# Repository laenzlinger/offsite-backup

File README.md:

# Granit — Offsite Backup Device

Custom carrier board for the Raspberry Pi CM4 Compute Module, designed as a minimal offsite backup appliance.

## Concept

A compact, headless device that connects to a remote network and receives encrypted backups onto an attached hard disk.
Designed to be left at a trusted offsite location (friend's house, office, etc.) and managed remotely.

This PCB is designed with [KiCad 10](https://www.kicad.org/blog/2026/03/Version-10.0.0-Released/)

## Hardware

### Core Components

| Component | Description |
|---|---|
| Raspberry Pi CM4 | Compute module (PCIe Gen 2 x1). CM5 mechanically compatible but not validated for power budget |
| ASM1061 | PCIe Gen 2 x1 to 2-port SATA III controller (no firmware blob required) |
| 2.5" or 3.5" SATA HDD/SSD | Backup storage |
| Amphenol 10029364-001LF | 22-pin SATA connector (data 7-pin + power 15-pin), right-angle |
| RJ45 + Ethernet magnetics | Gigabit Ethernet |
| DS3231 RTC | Battery-backed real-time clock with alarm wake (I2C) |
| CR2032 coin cell | RTC backup battery |
| RGB LED | Status indicator (idle/backup/error/maintenance) |
| Tactile button | Manual shutdown, trigger backup, enter maintenance mode on boot |
| Hirose DF40C-100DS-0.4V(51) | 2x CM4 board-to-board connectors |
| AP64501SP-13 | 3.5A DC-DC buck converter (reused from [pedalboard-hw](https://github.com/pedalboard/pedalboard-hw)) |
| USB-C | USB 2.0 OTG connector with USBLC6-2SC6 ESD protection |
| 2N7002 + 74AHCT1G32 | Hardware wake circuit (RTC alarm → GLOBAL_EN) and SATA power gate drivers |

### Block Diagram

### PCB 3D Render

### Key Design Decisions

- **ASM1061 over USB-to-SATA bridges**: Native PCIe SATA controller using the standard Linux
  `ahci` driver. No proprietary firmware blob required — the SPI flash footprint can be left
  unpopulated. SMART works natively (`smartctl /dev/sda`) without SAT translation hacks.
  Both CM4 and CM5 have PCIe Gen 2 x1, so full SATA III throughput is available on either
  module — unlike USB-to-SATA, which would be bottlenecked by CM4's USB 2.0 (~35 MB/s).
- **12V DC input**: Required for 3.5" HDD support (spindle motor needs 12V).
  12V is passed through directly to the SATA power connector.
  AP64501SP-13 accepts 3.8–28V input, so 12V is well within range.
  Both barrel jack (Würth 6941xx301002) and screw terminal (Phoenix MKDS-1,5-2) footprints
  are provided — populate one at assembly time.
- **Reuse from pedalboard-hw**: CM connector, power supply (AP64501SP-13 buck + NCP1117 LDO),
  USB power switch (AP2553W6), KiCad symbol/footprint library, CI pipeline.
- **USB-C OTG**: Single USB-C connector for eMMC flashing (`rpiboot`) and USB mass storage
  gadget mode (initial backup seeding over USB). USB 2.0 device mode only, with USBLC6-2SC6
  ESD protection.
- **SATA power control**: 12V and 5V to the SATA connector are software-controlled via
  GPIO17. HDD is off by default at boot — powered on explicitly by software. Solder jumpers
  (JP5, JP6) allow changing the default to power-on at boot without a PCB respin.
- **Power budget**: 12V @ 2A (3.5" HDD spin-up) + 5V @ 2.3A peak (CM4 + electronics) — use a 12V/3A+ PSU.
- **Boot and storage strategy**: Full OS on CM4 eMMC (no SD card slot), SATA HDD dedicated
  to LUKS-encrypted backup storage only. HDD can spin down when idle. No SD card — eMMC is
  more reliable for a deploy-and-forget device. Reflashing via `nRPIBOOT` + USB-C if needed.

For detailed circuit design notes, PCB routing guidelines, and netclass definitions,
see [hardware/DESIGN.md](hardware/DESIGN.md).

## Software

The device runs Raspberry Pi OS Lite (headless).

### Planned Stack

- Restic backup repository (encryption built-in)
- rsync to receive backups from NAS
- `smartmontools` for disk health monitoring (`smartctl /dev/sda`)
- WireGuard VPN for remote management
- RTC-based scheduled wake: DS3231 alarm → GPIO4 interrupt → CM wakes from suspend → backup runs → suspend
  (`GLOBAL_EN` tied high via pull-up, CM4 uses Linux `rtcwake` for suspend/resume.
  Hardware power-off wake via MOSFET latch on `GLOBAL_EN` planned for v2.)
- LUKS full-disk encryption on the backup drive
- Automatic drive mount and health monitoring

### HDD Power Control

GPIO17 (`SATA_PWR_EN`) controls the P-FET power switches for the SATA 12V and 5V rails.
The boot default is selected by solder jumpers JP5 and JP6 (see Design Considerations above).

**Connect sequence** (power on → detect → mount):
```bash
#!/bin/bash
# Power on SATA rails (GPIO high → N-FET on → P-FET gate low → P-FET on)
gpioset gpiochip0 17=1
sleep 2

# Rescan AHCI bus (ASM1061 hot-plug)
echo "- - -" > /sys/class/scsi_host/host0/scan
sleep 3

# Unlock and mount
cryptsetup luksOpen /dev/sda1 backup
mount /dev/mapper/backup /mnt/backup
```

**Disconnect sequence** (unmount → spin down → power off):
```bash
#!/bin/bash
# Unmount and close LUKS
umount /mnt/backup
cryptsetup luksClose backup

# Spin down platters
hdparm -Y /dev/sda
sleep 1

# Remove SCSI device before power cut
echo 1 > /sys/block/sda/device/delete

# Power off SATA rails (GPIO low → N-FET off → pull-up → P-FET off)
gpioset gpiochip0 17=0
```

### Deployment

1. Initial backup on-site: connect Granit to local network, run full backup over LAN
2. Move device to offsite location (friend's house, office, etc.)
3. Plug in Ethernet + power — done
4. Subsequent backups are incremental and run automatically over WireGuard

### Monitoring & Alerting

Monitoring must live outside the Granit device — if the device fails, it can't alert about
its own failure. The device reports in after each backup run using a dead man's switch pattern:

- After each successful backup, Granit pings a healthcheck endpoint (e.g. self-hosted or healthchecks.io)
- If the expected ping doesn't arrive, an alert is triggered (email, push notification)
- Reported metrics: backup success/failure, SMART disk health, disk space remaining
- WireGuard connectivity is implicitly monitored — no tunnel means no ping

## Enclosure

Metal enclosure designed for a plug-and-forget deployment. The device should be installable
by a non-technical person: plug in Ethernet, plug in power, done.

### Hammond 1455 Series

Same PCB (92 × 100mm) fits both cases, held by a 3D printed internal frame.
PCB and HDD sit side-by-side along the enclosure length, SATA connector direct-mates between them.

| | 1455L2201 (Slim) | 1455T2601 (Wide) |
|---|---|---|
| Dimensions | 220 × 103 × 30.5 mm | 260 × 160 × 51.5 mm |
| Internal width | ~100 mm | ~157 mm |
| Internal height | ~27 mm | ~48 mm |
| HDD support | 2.5" only | 2.5" or 3.5" |
| Material | Extruded aluminium | Extruded aluminium |
| Colors | Natural, Black, Blue, Red | Natural, Black, Blue, Red |
| Assembly |  |  |

### Requirements

- Cutouts: barrel jack or screw terminal (12V), RJ45 (Ethernet), USB-C
- Tactile button accessible from outside (recessed to prevent accidental press)
- RGB LED visible through enclosure (light pipe or translucent window)
- Thermal pad or heatsink contact for CM4 SoC to enclosure lid
- Internal mounting for 2.5" or 3.5" HDD (M4 mounting holes)
- PCB standoffs (M3 mounting holes)

## Generated Hardware Documentation

Browse the latest generated outputs at **[laenzlinger.github.io/granit](https://laenzlinger.github.io/granit/)**.

Includes schematic PDF, interactive BOM, HTML BOM, and PCB prints — auto-generated on every push with [KiBot](https://github.com/INTI-CMNB/KiBot) (dev branch) running inside the official [kicad/kicad:10.0](https://hub.docker.com/r/kicad/kicad) container.

## License

[CERN Open Hardware Licence Version 2 - Permissive](https://ohwr.org/cern_ohl_p_v2.txt)

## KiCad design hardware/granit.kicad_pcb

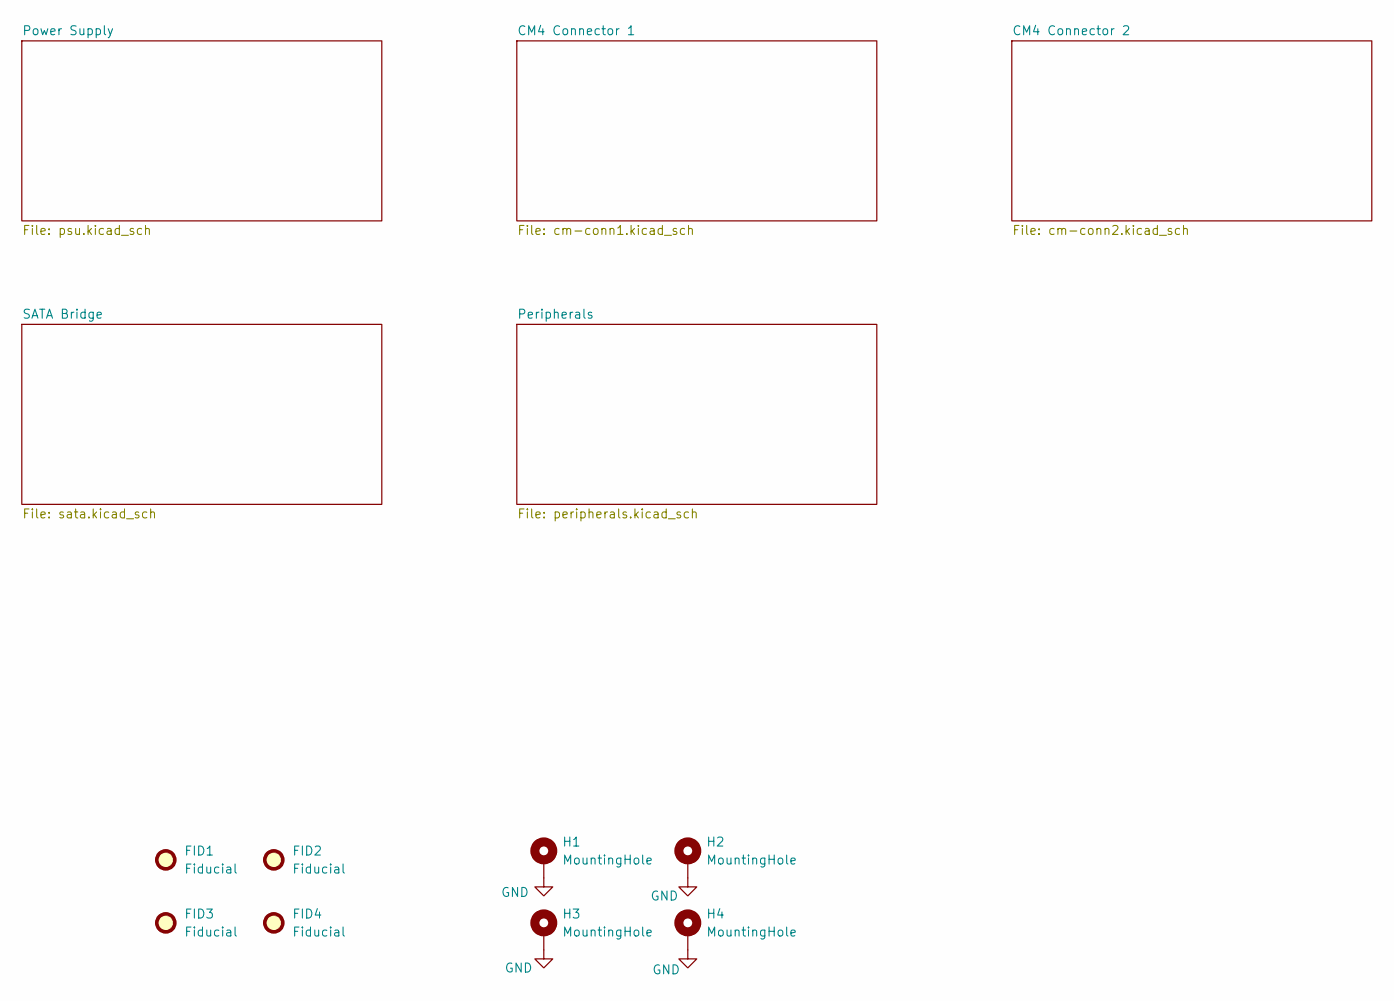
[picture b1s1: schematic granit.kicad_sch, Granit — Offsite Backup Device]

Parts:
FID1, FID2, FID3, FID4: Fiducial; Fiducial_1mm_Mask2mm
H1, H2, H3, H4: MountingHole; MountingHole_3.2mm_M3_Pad_Via

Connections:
GND: H1.1 (1_1), H2.1 (1_1), H3.1 (1_1), H4.1 (1_1); also elsewhere on the board

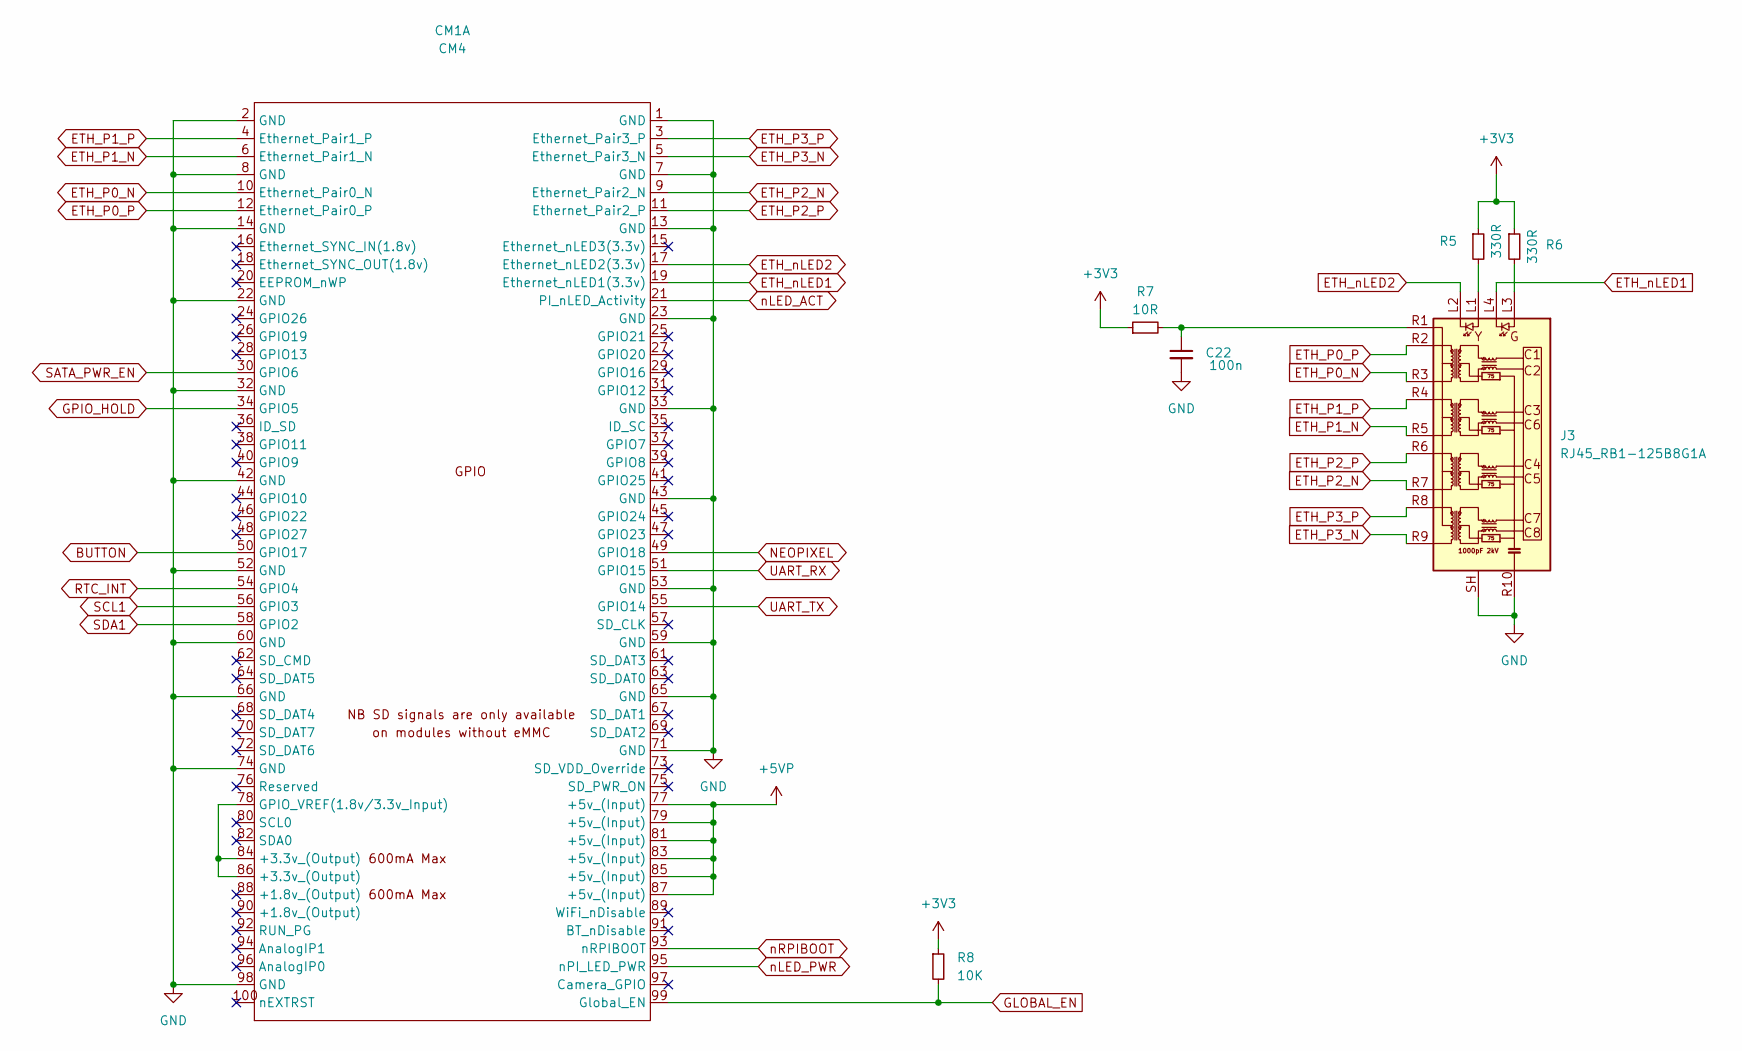
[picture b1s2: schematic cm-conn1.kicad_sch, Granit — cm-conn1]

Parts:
C22: 100n; C_0805_2012Metric; Digikey 1276-1180-1-ND
CM1: CM4; Raspberry-Pi-4-Compute-Module
J3: RJ45_RB1-125B8G1A; RJ45_UDE_RB1-125B8G1A
R5, R6: 330R; R_0805_2012Metric
R7: 10R; R_0805_2012Metric
R8: 10K; R_0805_2012Metric

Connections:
+3V3: R5.1, R6.1, R7.1, R8.1; also elsewhere on the board
+5VP: CM1.77 (+5v_(Input)), CM1.79 (+5v_(Input)), CM1.81 (+5v_(Input)), CM1.83 (+5v_(Input)), CM1.85 (+5v_(Input)), CM1.87 (+5v_(Input)); also elsewhere on the board
BUTTON: CM1.50 (GPIO17); also elsewhere on the board
ETH_P0_N: CM1.10 (Ethernet_Pair0_N), J3.R3 (TD1-)
ETH_P0_P: CM1.12 (Ethernet_Pair0_P), J3.R2 (TD1+)
ETH_P1_N: CM1.6 (Ethernet_Pair1_N), J3.R5 (TD2-)
ETH_P1_P: CM1.4 (Ethernet_Pair1_P), J3.R4 (TD2+)
ETH_P2_N: CM1.9 (Ethernet_Pair2_N), J3.R7 (TD3-)
ETH_P2_P: CM1.11 (Ethernet_Pair2_P), J3.R6 (TD3+)
ETH_P3_N: CM1.5 (Ethernet_Pair3_N), J3.R9 (TD4-)
ETH_P3_P: CM1.3 (Ethernet_Pair3_P), J3.R8 (TD4+)
ETH_nLED1: CM1.19 (Ethernet_nLED1(3.3v)), J3.L4
ETH_nLED2: CM1.17 (Ethernet_nLED2(3.3v)), J3.L2
GLOBAL_EN: CM1.99 (Global_EN), R8.2; also elsewhere on the board
GND: C22.2, CM1.1 (GND), CM1.2 (GND), CM1.7 (GND), CM1.8 (GND), CM1.13 (GND), CM1.14 (GND), CM1.22 (GND), CM1.23 (GND), CM1.32 (GND), CM1.33 (GND), CM1.42 (GND), CM1.43 (GND), CM1.52 (GND), CM1.53 (GND), CM1.59 (GND), CM1.60 (GND), CM1.65 (GND), CM1.66 (GND), CM1.71 (GND), CM1.74 (GND), CM1.98 (GND), J3.R10 (GND), J3.SH; also elsewhere on the board
NEOPIXEL: CM1.49 (GPIO18); also elsewhere on the board
unnamed: CM1.78 (GPIO_VREF(1.8v/3.3v_Input)), CM1.84 (+3.3v_(Output)), CM1.86 (+3.3v_(Output))
unnamed: C22.1, J3.R1 (CT), R7.2
unnamed: J3.L1, R5.2
unnamed: J3.L3, R6.2
RTC_INT: CM1.54 (GPIO4); also elsewhere on the board
SCL1: CM1.56 (GPIO3); also elsewhere on the board
SDA1: CM1.58 (GPIO2); also elsewhere on the board
UART_RX: CM1.51 (GPIO15); also elsewhere on the board
UART_TX: CM1.55 (GPIO14); also elsewhere on the board
nLED_ACT: CM1.21 (PI_nLED_Activity); also elsewhere on the board
nLED_PWR: CM1.95 (nPI_LED_PWR); also elsewhere on the board
nRPIBOOT: CM1.93 (nRPIBOOT); also elsewhere on the board

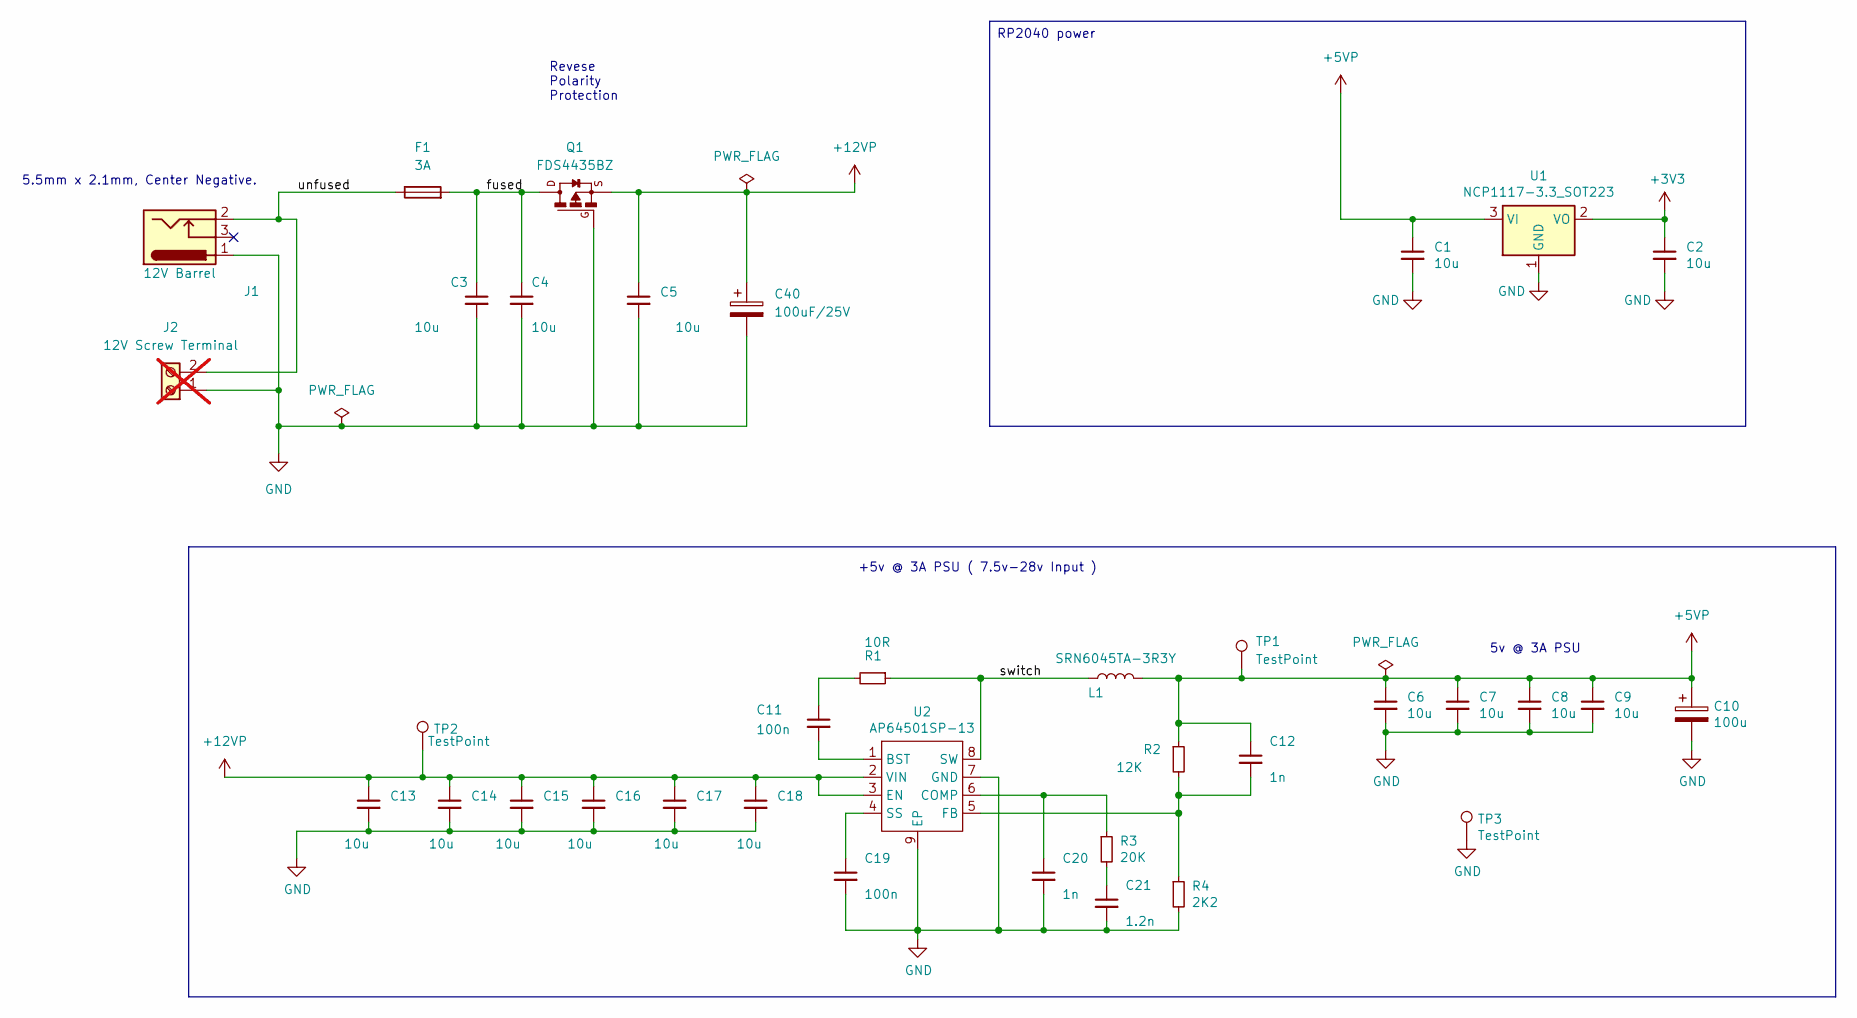
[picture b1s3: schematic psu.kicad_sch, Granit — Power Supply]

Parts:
C1, C2, C3, C4, C5, C6, C7, C8, C9, C13, C14, C15, C16, C17, C18: 10u; C_0805_2012Metric
C10: 100u; CP_EIA-7343-31_Kemet-D
C11, C19: 100n; C_0805_2012Metric; Digikey 1276-1180-1-ND
C12, C20: 1n; C_0805_2012Metric
C21: 1.2n; C_0805_2012Metric
C40: 100uF/25V; CP_Elec_6.3x5.8
F1: 3A; Fuse_2512_6332Metric
J1: 12V Barrel; BarrelJack_Wuerth_6941xx301002
J2: 12V Screw Terminal; TerminalBlock_Phoenix_MKDS-1,5-2_1x02_P5.00mm_Horizontal; not fitted
L1: SRN6045TA-3R3Y; L_Bourns_SRN6045TA
Q1: FDS4435BZ; SO08-E3
R1: 10R; R_0805_2012Metric
R2: 12K; R_0805_2012Metric
R3: 20K; R_0805_2012Metric
R4: 2K2; R_0805_2012Metric
TP1, TP2, TP3: TestPoint; TestPoint_Pad_2.0x2.0mm
U1: NCP1117-3.3_SOT223; SOT-223-3_TabPin2
U2: AP64501SP-13; SOIC-8-1EP_3.9x4.9mm_P1.27mm_EP2.95x4.9mm_Mask2.71x3.4mm_Th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

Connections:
+3V3: C2.1, U1.2 (VO); also elsewhere on the board
+5VP: C1.1, C6.1, C7.1, C8.1, C9.1, C10.1, C12.1, L1.2, R2.1, TP1.1 (1_1), U1.3 (VI); also elsewhere on the board
+12VP: C5.1, C13.1, C14.1, C15.1, C16.1, C17.1, C18.1, C40.1, Q1.1-3, TP2.1 (1_1), U2.2 (VIN), U2.3 (EN); also elsewhere on the board
/Power Supply/fused: C3.1, C4.1, F1.2, Q1.5-8
/Power Supply/switch: L1.1, R1.1, U2.8 (SW)
/Power Supply/unfused: F1.1, J1.2, J2.2
GND: C1.2, C2.2, C3.2, C4.2, C5.2, C6.2, C7.2, C8.2, C9.2, C10.2, C13.2, C14.2, C15.2, C16.2, C17.2, C18.2, C19.2, C20.2, C21.2, C40.2, J1.1, J2.1, Q1.4, R4.2, TP3.1 (1_1), U1.1 (GND), U2.7 (GND), U2.9 (EP); also elsewhere on the board
unnamed: C11.1, R1.2
unnamed: C21.1, R3.2
unnamed: C11.2, U2.1 (BST)
unnamed: C20.1, R3.1, U2.6 (COMP)
unnamed: C12.2, R2.2, R4.1, U2.5 (FB)
unnamed: C19.1, U2.4 (SS)

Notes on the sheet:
5v @ 3A PSU
+5v @ 3A PSU ( 7.5v-28v Input )
Revese Polarity Protection
5.5mm x 2.1mm, Center Negative.
RP2040 power

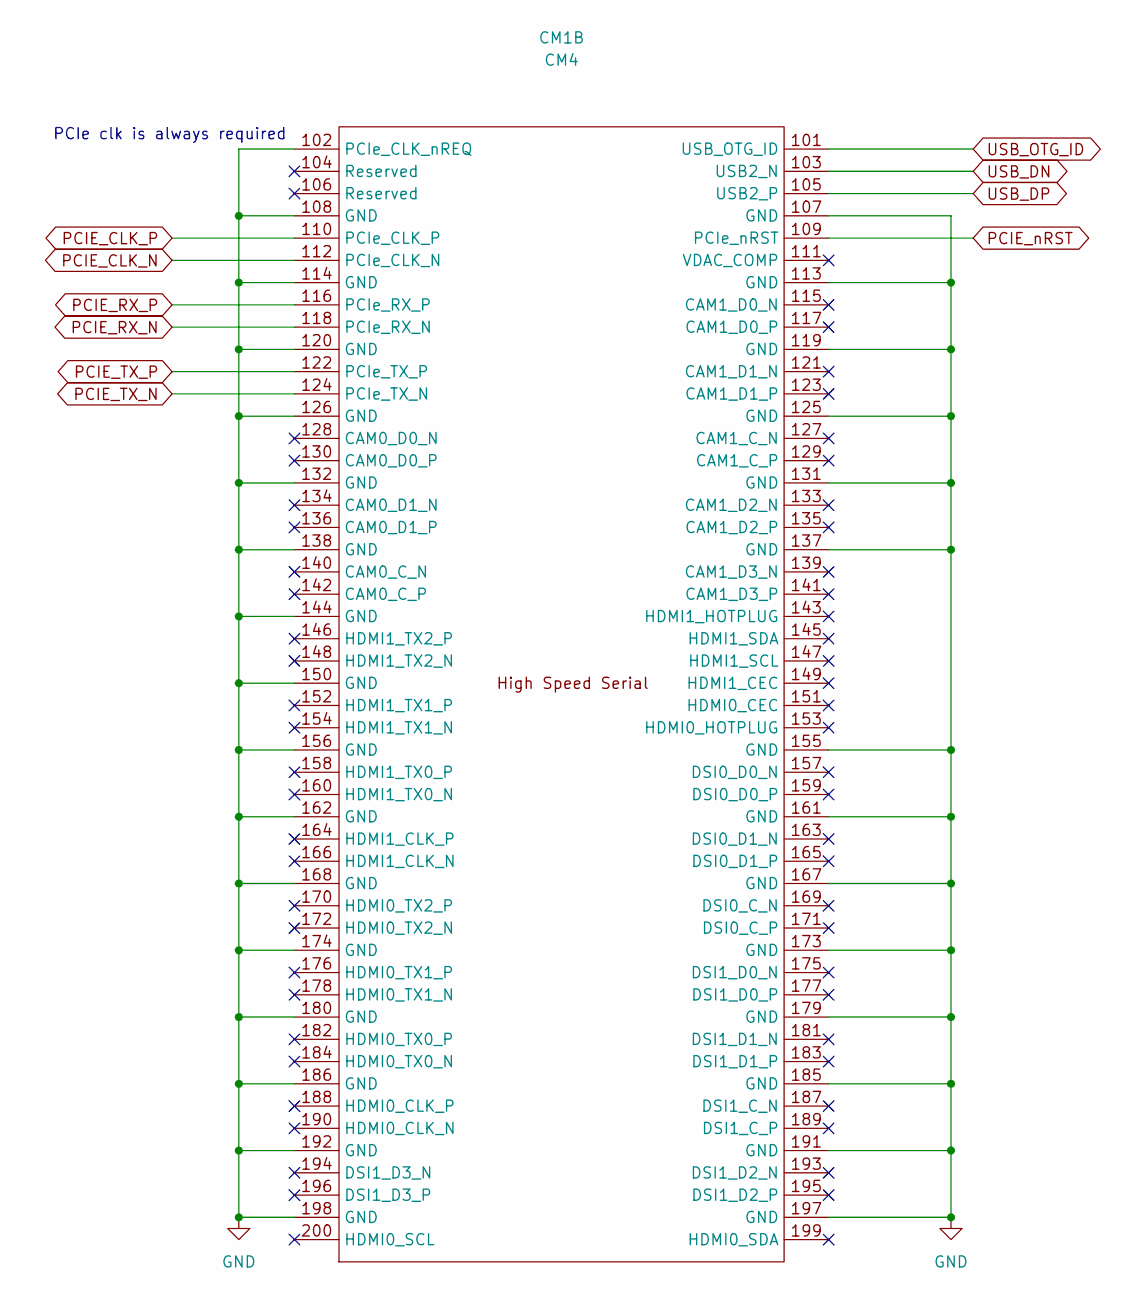
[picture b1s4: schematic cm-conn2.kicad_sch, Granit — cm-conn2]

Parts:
CM1: CM4; Raspberry-Pi-4-Compute-Module

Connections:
GND: CM1.102 (PCIe_CLK_nREQ), CM1.107 (GND), CM1.108 (GND), CM1.113 (GND), CM1.114 (GND), CM1.119 (GND), CM1.120 (GND), CM1.125 (GND), CM1.126 (GND), CM1.131 (GND), CM1.132 (GND), CM1.137 (GND), CM1.138 (GND), CM1.144 (GND), CM1.150 (GND), CM1.155 (GND), CM1.156 (GND), CM1.161 (GND), CM1.162 (GND), CM1.167 (GND), CM1.168 (GND), CM1.173 (GND), CM1.174 (GND), CM1.179 (GND), CM1.180 (GND), CM1.185 (GND), CM1.186 (GND), CM1.191 (GND), CM1.192 (GND), CM1.197 (GND), CM1.198 (GND); also elsewhere on the board
PCIE_CLK_N: CM1.112 (PCIe_CLK_N); also elsewhere on the board
PCIE_CLK_P: CM1.110 (PCIe_CLK_P); also elsewhere on the board
PCIE_RX_N: CM1.118 (PCIe_RX_N); also elsewhere on the board
PCIE_RX_P: CM1.116 (PCIe_RX_P); also elsewhere on the board
PCIE_TX_N: CM1.124 (PCIe_TX_N); also elsewhere on the board
PCIE_TX_P: CM1.122 (PCIe_TX_P); also elsewhere on the board
PCIE_nRST: CM1.109 (PCIe_nRST); also elsewhere on the board
USB_DN: CM1.103 (USB2_N); also elsewhere on the board
USB_DP: CM1.105 (USB2_P); also elsewhere on the board
USB_OTG_ID: CM1.101 (USB_OTG_ID); also elsewhere on the board

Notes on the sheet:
PCIe clk is always required

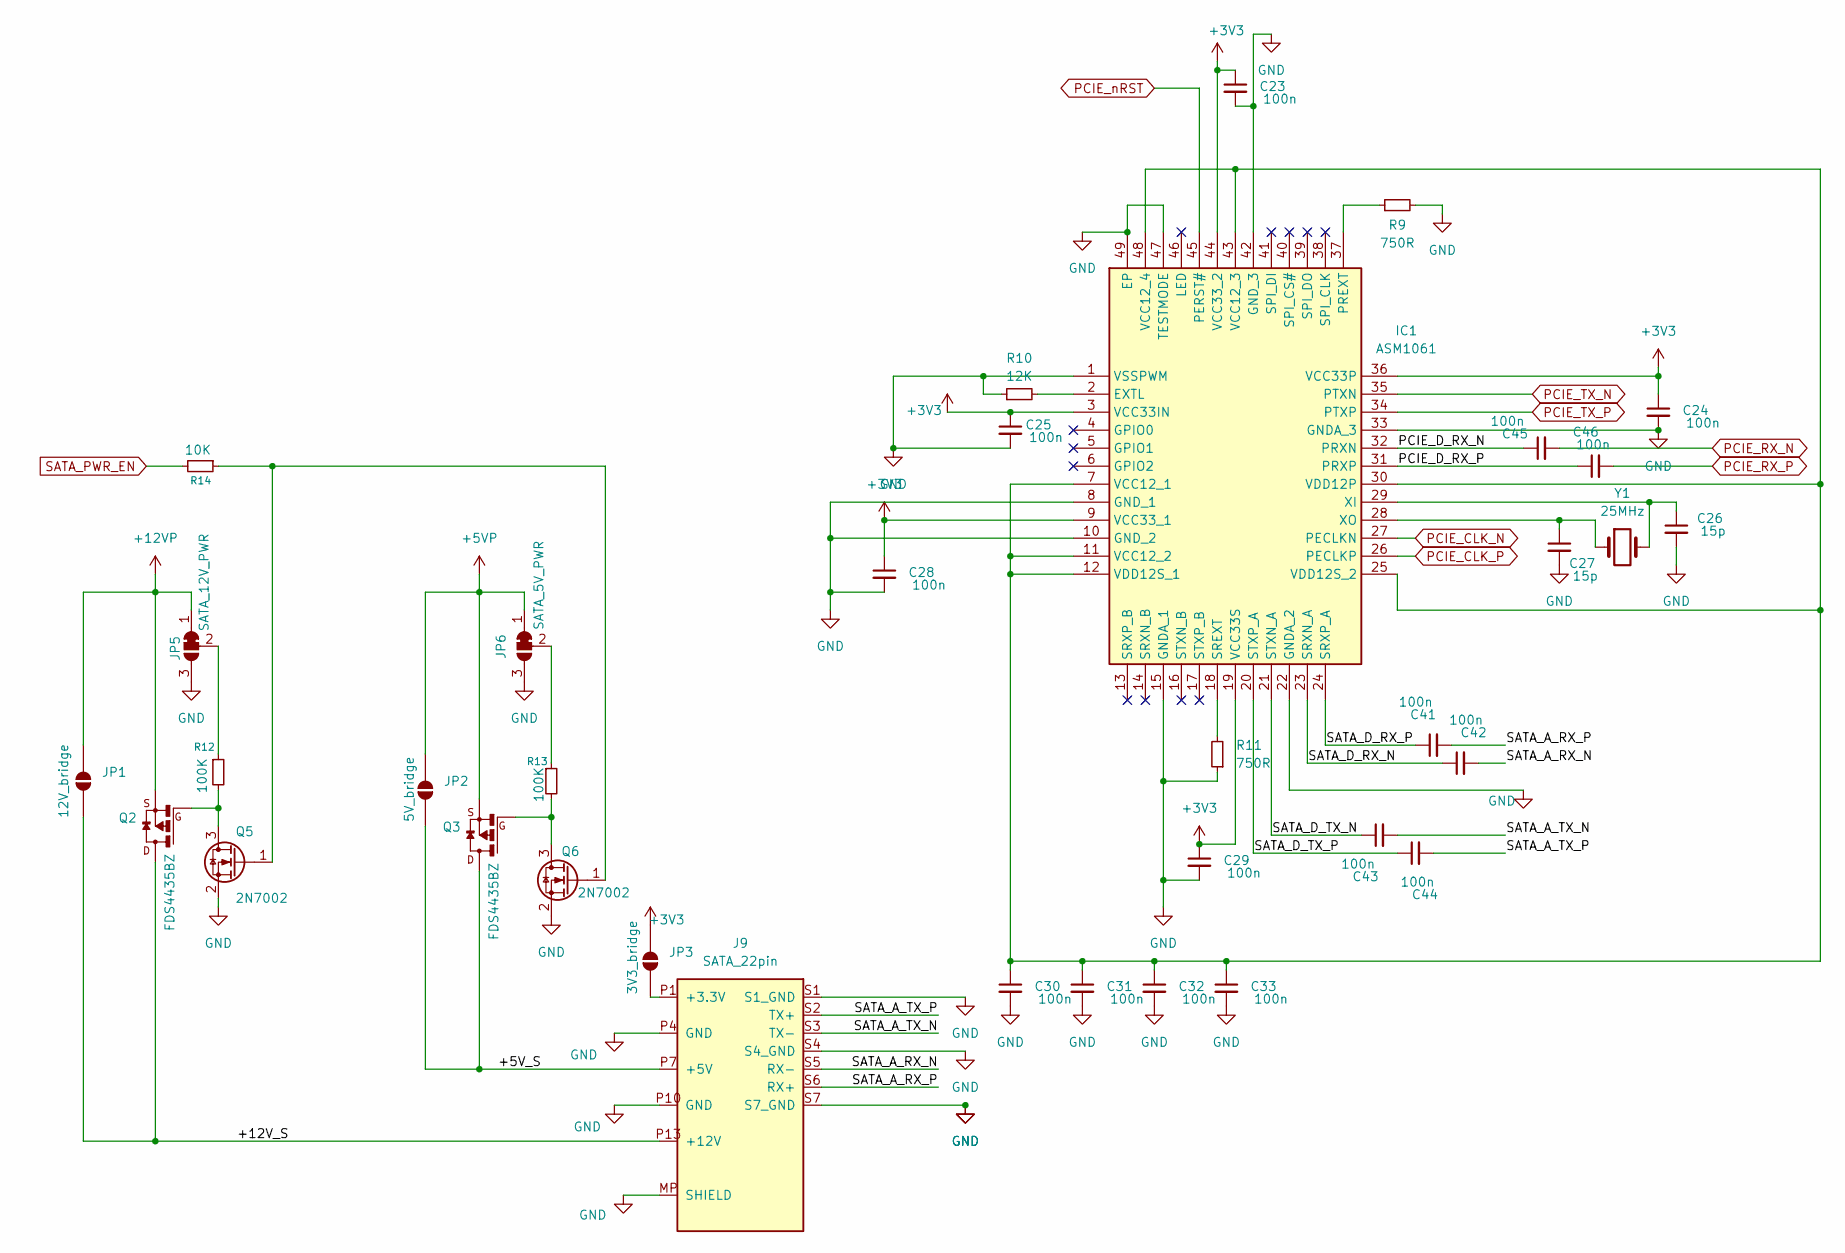
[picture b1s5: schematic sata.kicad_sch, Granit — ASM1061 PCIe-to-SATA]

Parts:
C23, C24, C25, C28, C29, C30, C31, C32, C33, C41, C42, C43, C44, C45, C46: 100n; C_0805_2012Metric; Digikey 1276-1180-1-ND
C26, C27: 15p; C_0805_2012Metric; Digikey 1276-1180-1-ND
IC1: ASM1061; QFN50P700X700X90-49N-D; Manufacturer_Part_Number ASM1061
J9: SATA_22pin; SATA_Amphenol_10029364-001LF_Horizontal
JP1: 12V_bridge; SolderJumper-2_P1.3mm_Open_Pad1.0x1.5mm
JP2: 5V_bridge; SolderJumper-2_P1.3mm_Open_Pad1.0x1.5mm
JP3: 3V3_bridge; SolderJumper-2_P1.3mm_Open_Pad1.0x1.5mm
JP5: SATA_12V_PWR; SolderJumper-3_P1.3mm_Bridged12_Pad1.0x1.5mm
JP6: SATA_5V_PWR; SolderJumper-3_P1.3mm_Bridged12_Pad1.0x1.5mm
Q2, Q3: FDS4435BZ; SO08-E3
Q5, Q6: 2N7002; SOT-23
R9, R11: 750R; R_0805_2012Metric
R10: 12K; R_0805_2012Metric
R12, R13: 100K; R_0805_2012Metric
R14: 10K; R_0805_2012Metric
Y1: 25MHz; Crystal_SMD_3215-2Pin_3.2x1.5mm

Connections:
+3V3: C23.1, C24.1, C25.1, C28.1, C29.1, IC1.3 (VCC33IN), IC1.9 (VCC33_1), IC1.19 (VCC33S), IC1.36 (VCC33P), IC1.44 (VCC33_2), JP3.2 (B); also elsewhere on the board
+5VP: JP2.2 (B), JP6.1 (A), Q3.1-3; also elsewhere on the board
+12VP: JP1.2 (B), JP5.1 (A), Q2.1-3; also elsewhere on the board
/SATA Bridge/+5V_S: J9.P7 (+5V), J9.P8 (+5V), J9.P9 (+5V), JP2.1 (A), Q3.5-8
/SATA Bridge/+12V_S: J9.P13 (+12V), J9.P14 (+12V), J9.P15 (+12V), JP1.1 (A), Q2.5-8
/SATA Bridge/PCIE_D_RX_N: C45.1, IC1.32 (PRXN)
/SATA Bridge/PCIE_D_RX_P: C46.1, IC1.31 (PRXP)
/SATA Bridge/SATA_A_RX_N: C42.2, J9.S5 (RX-)
/SATA Bridge/SATA_A_RX_P: C41.2, J9.S6 (RX+)
/SATA Bridge/SATA_A_TX_N: C43.2, J9.S3 (TX-)
/SATA Bridge/SATA_A_TX_P: C44.2, J9.S2 (TX+)
/SATA Bridge/SATA_D_RX_N: C42.1, IC1.23 (SRXN_A)
/SATA Bridge/SATA_D_RX_P: C41.1, IC1.24 (SRXP_A)
/SATA Bridge/SATA_D_TX_N: C43.1, IC1.21 (STXN_A)
/SATA Bridge/SATA_D_TX_P: C44.1, IC1.20 (STXP_A)
GND: C23.2, C24.2, C25.2, C26.2, C27.2, C28.2, C29.2, C30.2, C31.2, C32.2, C33.2, IC1.1 (VSSPWM), IC1.8 (GND_1), IC1.10 (GND_2), IC1.15 (GNDA_1), IC1.22 (GNDA_2), IC1.33 (GNDA_3), IC1.42 (GND_3), IC1.47 (TESTMODE), IC1.49 (EP), J9.MP (SHIELD), J9.P4 (GND), J9.P5 (GND), J9.P6 (GND), J9.P10 (GND), J9.P11 (GND), J9.P12 (GND), J9.S1 (S1_GND), J9.S4 (S4_GND), J9.S7 (S7_GND), JP5.3 (B), JP6.3 (B), Q5.2 (S), Q6.2 (S), R9.2, R10.1, R11.1; also elsewhere on the board
unnamed: IC1.2 (EXTL), R10.2
unnamed: IC1.37 (PREXT), R9.1
unnamed: IC1.18 (SREXT), R11.2
unnamed: C30.1, C31.1, C32.1, C33.1, IC1.7 (VCC12_1), IC1.11 (VCC12_2), IC1.12 (VDD12S_1), IC1.25 (VDD12S_2), IC1.30 (VDD12P), IC1.43 (VCC12_3), IC1.48 (VCC12_4)
unnamed: C26.1, IC1.29 (XI), Y1.2
unnamed: C27.1, IC1.28 (XO), Y1.1
unnamed: J9.P1 (+3.3V), J9.P2 (+3.3V), J9.P3 (+3.3V), JP3.1 (A)
unnamed: JP5.2 (C), R12.1
unnamed: JP6.2 (C), R13.1
unnamed: Q2.4, Q5.3 (D), R12.2
unnamed: Q5.1 (G), Q6.1 (G), R14.1
unnamed: Q3.4, Q6.3 (D), R13.2
PCIE_CLK_N: IC1.27 (PECLKN); also elsewhere on the board
PCIE_CLK_P: IC1.26 (PECLKP); also elsewhere on the board
PCIE_RX_N: C45.2; also elsewhere on the board
PCIE_RX_P: C46.2; also elsewhere on the board
PCIE_TX_N: IC1.35 (PTXN); also elsewhere on the board
PCIE_TX_P: IC1.34 (PTXP); also elsewhere on the board
PCIE_nRST: IC1.45 (PERST#); also elsewhere on the board

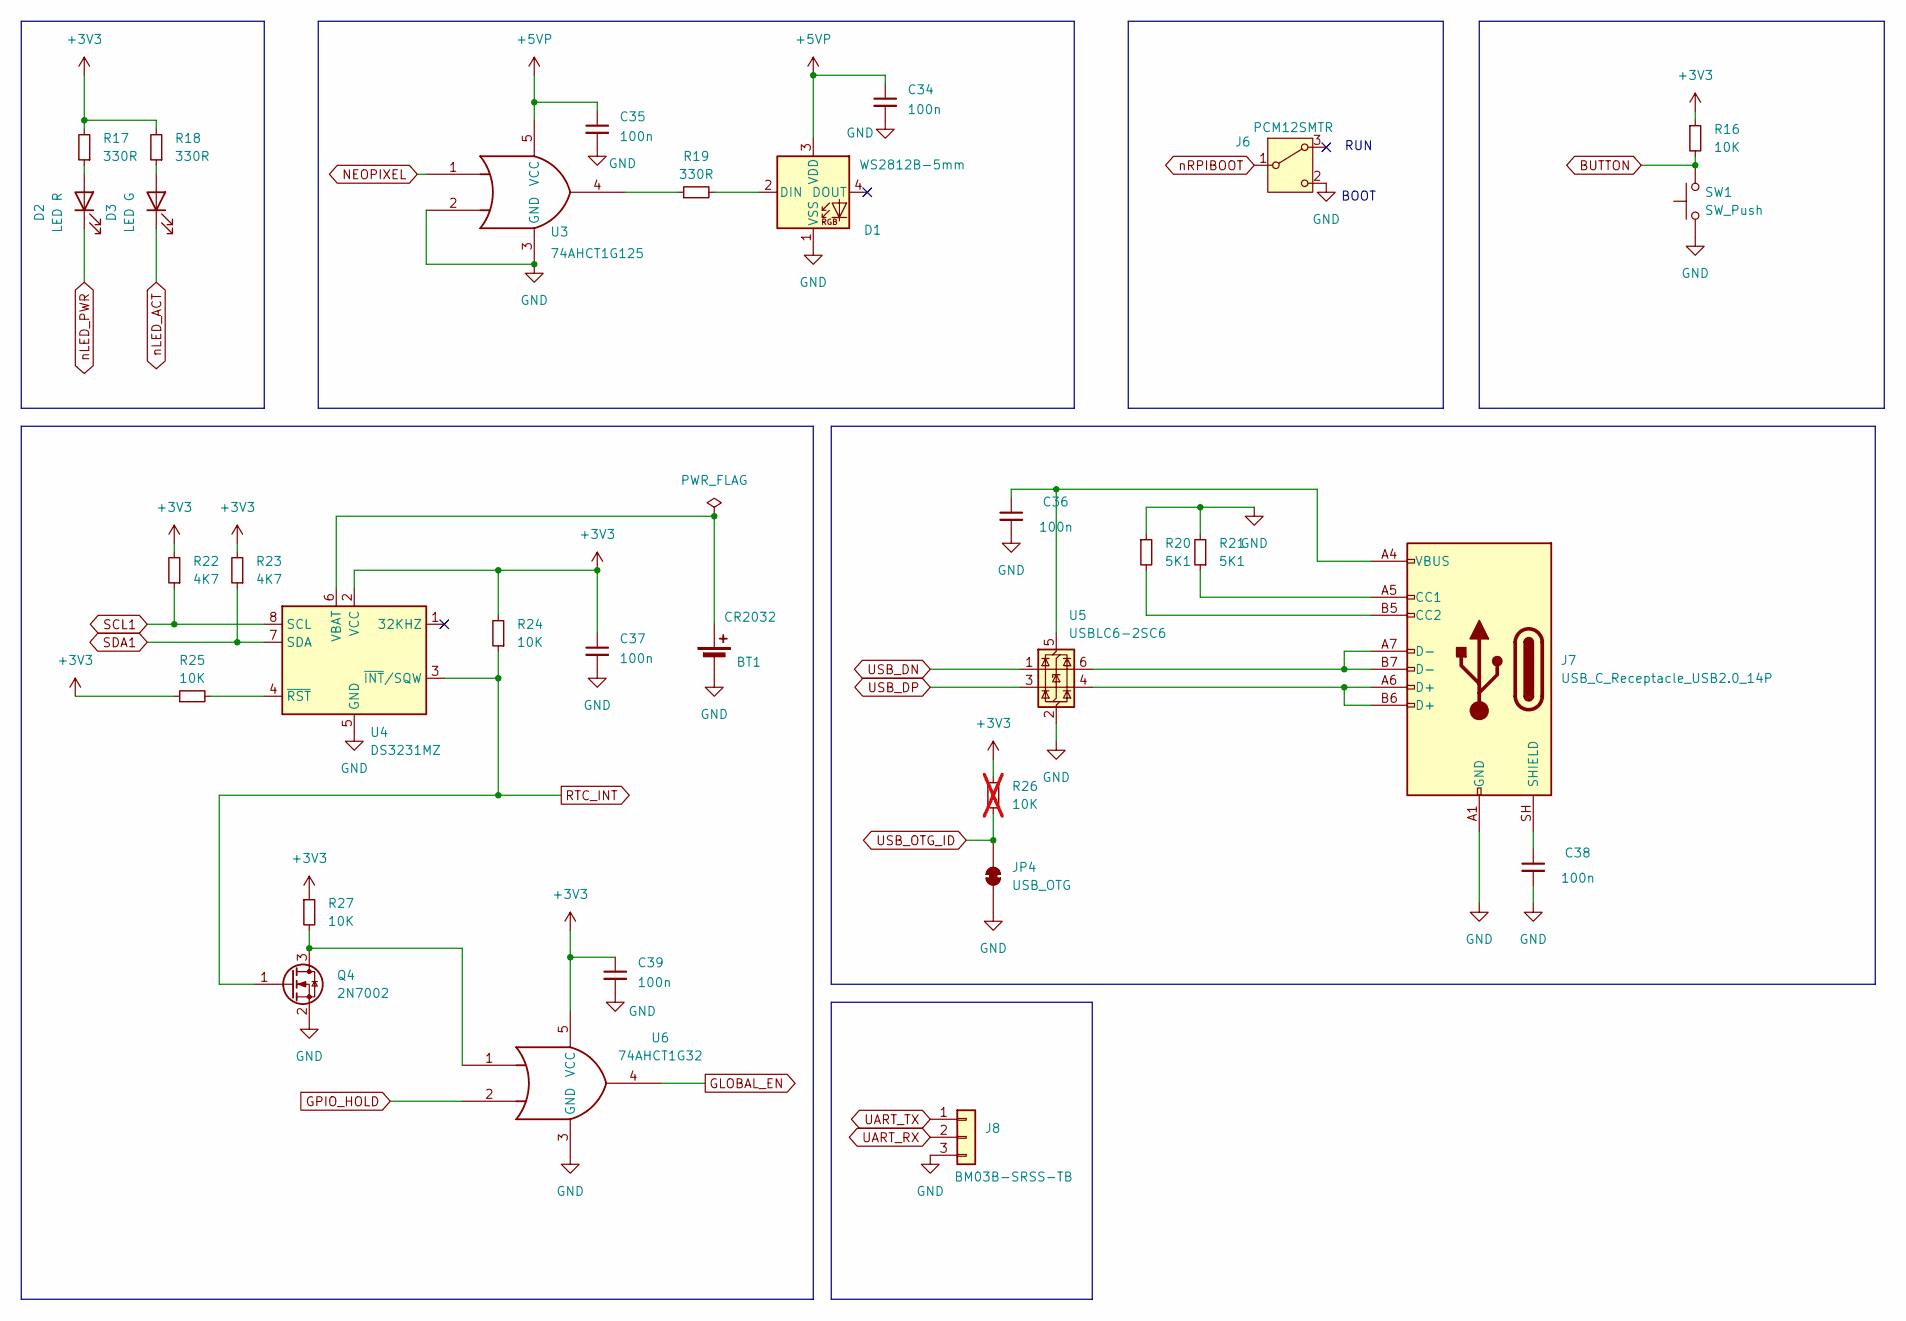
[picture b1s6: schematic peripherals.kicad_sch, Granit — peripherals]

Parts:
BT1: CR2032; BatteryHolder_Keystone_103_1x20mm
C34, C35, C36, C37, C38, C39: 100n; C_0805_2012Metric; Digikey 1276-1180-1-ND
D1: WS2812B-5mm; LED_WS2812B_PLCC4_5.0x5.0mm_P3.2mm
D2: LED R; LED_0805_2012Metric
D3: LED G; LED_0805_2012Metric
J6: PCM12SMTR; SW_SPDT_PCM12
J7: USB_C_Receptacle_USB2.0_14P; USB_C_Receptacle_GCT_USB4105-xx-A_16P_TopMnt_Horizontal
J8: BM03B-SRSS-TB; JST_SH_BM03B-SRSS-TB_1x03-1MP_P1.00mm_Vertical
JP4: USB_OTG; SolderJumper-2_P1.3mm_Bridged_Pad1.0x1.5mm
Q4: 2N7002; SOT-23
R16, R24, R25, R27: 10K; R_0805_2012Metric
R17, R18, R19: 330R; R_0805_2012Metric
R20, R21: 5K1; R_0805_2012Metric
R22, R23: 4K7; R_0805_2012Metric
R26: 10K; R_0805_2012Metric; not fitted
SW1: SW_Push; SW_Push_1P1T-MP_NO_Horizontal_Alps_SKRTLAE010
U3: 74AHCT1G125; SOT-23-5
U4: DS3231MZ; SOIC-8_3.9x4.9mm_P1.27mm
U5: USBLC6-2SC6; SOT-23-6
U6: 74AHCT1G32; SOT-23-5

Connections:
+3V3: C37.1, C39.1, R16.1, R17.2, R18.2, R22.2, R23.2, R24.2, R25.1, R26.1, R27.1, U4.2 (VCC), U6.5 (VCC); also elsewhere on the board
+5VP: C34.1, C35.1, D1.3 (VDD), U3.5 (VCC); also elsewhere on the board
BUTTON: R16.2, SW1.2; also elsewhere on the board
GLOBAL_EN: U6.4; also elsewhere on the board
GND: BT1.2 (-), C34.2, C35.2, C36.2, C37.2, C38.2, C39.2, D1.1 (VSS), J6.2 (C), J7.A1 (GND), J7.A12 (GND), J7.B1 (GND), J7.B12 (GND), J8.3, JP4.1 (A), Q4.2 (S), R20.1, R21.2, SW1.1, U3.2, U3.3 (GND), U4.5 (GND), U5.2 (GND), U6.3 (GND); also elsewhere on the board
NEOPIXEL: U3.1; also elsewhere on the board
unnamed: BT1.1 (+), U4.6 (VBAT)
unnamed: D1.2 (DIN), R19.2
unnamed: D2.2 (A), R17.1
unnamed: D3.2 (A), R18.1
unnamed: J7.A5 (CC1), R21.1
unnamed: J7.B5 (CC2), R20.2
unnamed: J7.A6 (D+), J7.B6 (D+), U5.4 (I/O2)
unnamed: J7.A7 (D-), J7.B7 (D-), U5.6 (I/O1)
unnamed: C38.1, J7.SH (SHIELD)
unnamed: Q4.3 (D), R27.2, U6.1
unnamed: R19.1, U3.4
unnamed: R25.2, U4.4 (~RST)
unnamed: C36.1, J7.A4 (VBUS), J7.A9 (VBUS), J7.B4 (VBUS), J7.B9 (VBUS), U5.5 (VBUS)
RTC_INT: Q4.1 (G), R24.1, U4.3 (~INT/SQW); also elsewhere on the board
SCL1: R22.1, U4.8 (SCL); also elsewhere on the board
SDA1: R23.1, U4.7 (SDA); also elsewhere on the board
UART_RX: J8.2; also elsewhere on the board
UART_TX: J8.1; also elsewhere on the board
USB_DN: U5.1 (I/O1); also elsewhere on the board
USB_DP: U5.3 (I/O2); also elsewhere on the board
USB_OTG_ID: JP4.2 (B), R26.2; also elsewhere on the board
nLED_ACT: D3.1 (K); also elsewhere on the board
nLED_PWR: D2.1 (K); also elsewhere on the board
nRPIBOOT: J6.1 (B); also elsewhere on the board

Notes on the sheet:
BOOT
RUN

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
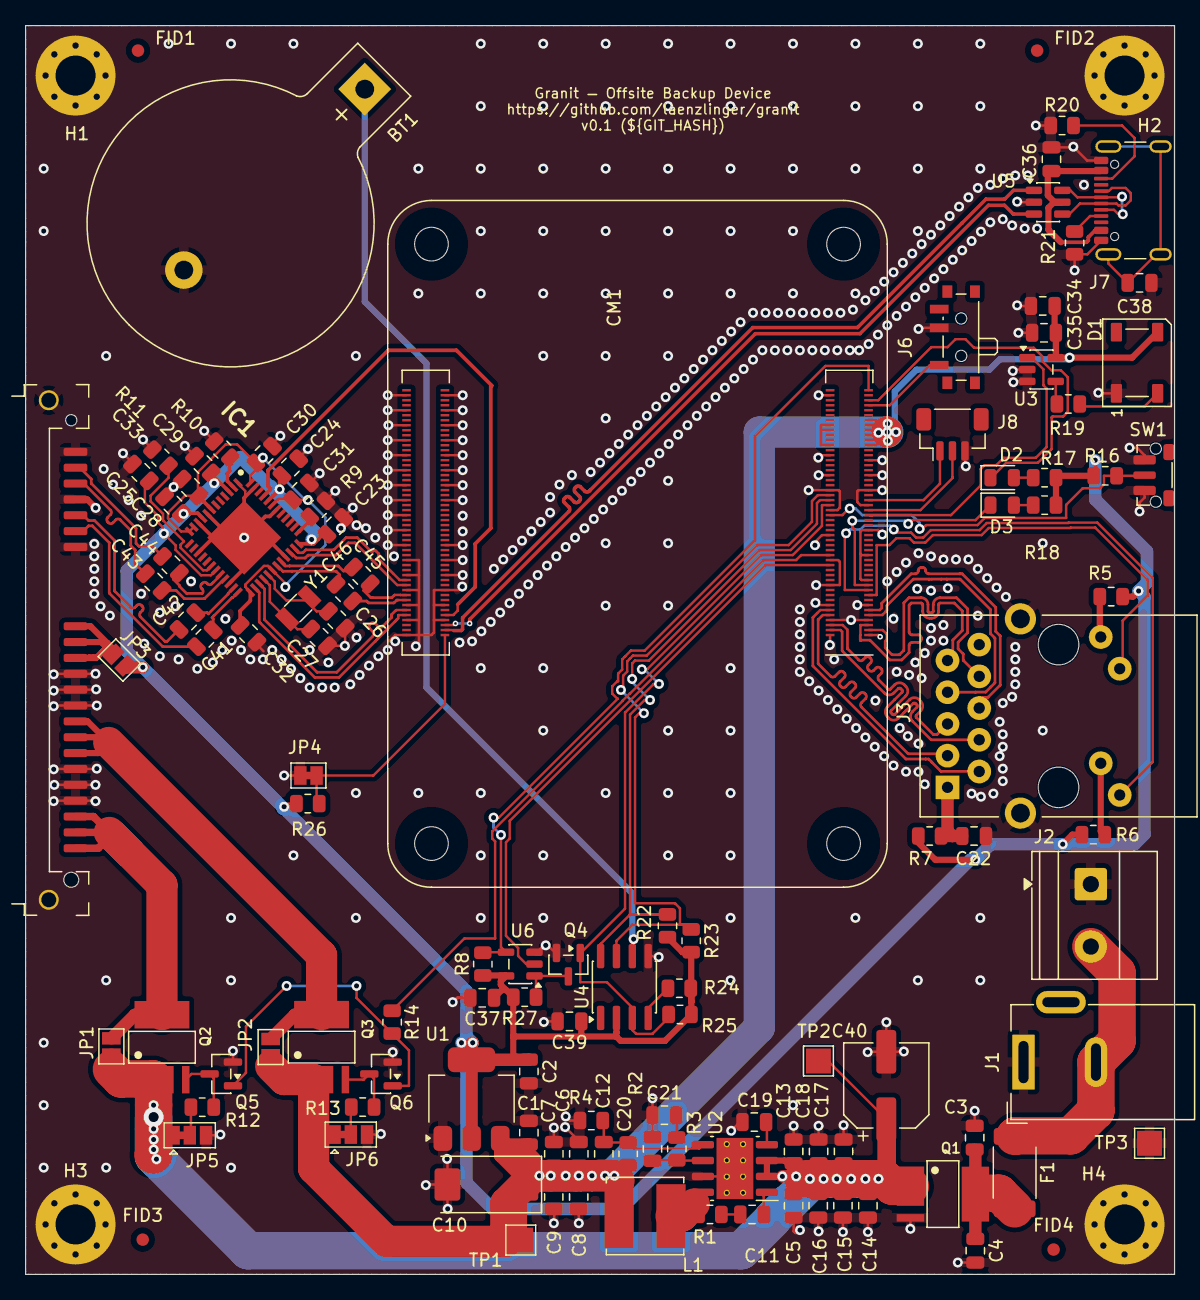
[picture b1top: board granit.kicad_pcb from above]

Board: 4 copper layers, 92.0 x 100.0 mm, 118 parts (0 on the bottom side), 87 nets.
